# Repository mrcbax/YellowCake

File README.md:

# YellowCake

YellowCake is a UMW CPSC 491 project to create an open source, inexpensive, small footprint, single board, POSIX computer. YellowCake will be similar to a Raspberry Pi. The primary goal of the YellowCake project is learning. A secondary goal is to create a product that is used by others.

The members of the YellowCake team are the following.
- Gusty Cooper - faculty sponsor
- Chad Baxter - student researcher
- Collin Mistr - student researcher

Gusty is an experienced software developer and systems engineer. Chad and Collin are talented computer science students with lots of experience in electronic board design. They have designed several boards that fix problems in various MacBook computers. Their design solutions included board layout and subsequent manufacture by a foundry. Collin and Chad are selling their MacBook solutions on Ebay. A few of of their solutions are described at: 

- https://computeco.de/DyingLight
- https://computeco.de/MuxHat

## YellowCake Executive Summary

YellowCake is a research project to create an open source, single board computer similar to a Raspberry Pi. Chad and Collin will learn the fundamentals of building a computer, which include selecting a form factor of the board, selecting electronic components for a computer, designing communication among components, layout components on the board, printing the board, assembling a computer on the board, testing the computer, and establishing a LINUX operating system on the computer. The following is a picture of a Raspberry Pi single board computer.

## YellowCake Goals

YellowCake is a three credit CPSC 491, which occurs during Fall 2019. The goals for YellowCake are the following.
- Provide an environment in which Chad and Collin can significantly increase their CPSC skills and knowledge as related to computer architecture, design of single board computers, integration of electronics on single board computers, testing single board computers, and hosting and OS on single board computers.
- Complete the design YellowCake - the design is to be documented as open source.
- Complete the YellowCake board layout in a manufacturing format using the board CAD software KiCad: http://kicad-pcb.org/ - the layout is to be documented as open source.
- Complete a prototype of YellowCake - follow the process in YellowCake Design and Development Process to implement a prototype that demonstrates the design.

## YellowCake Prework

During Spring 2019, the YellowCake team will meet periodically to discuss the project, make preliminary decisions, define the parameters for CPSC 491 YellowCake, and submit funding requests. 
YellowCake Design Parameters
We have begun preliminary design, creating various design parameters. Design parameters are subject to change. The design parameters defined thus far are the following.
- YellowCake board.
  - Footprint will be small similar in size to Raspberry Pi.
  - YellowCake board footprint will adhere to a standard. The following are candidates.
     - PCI / 104 - Express:  https://pc104.org/hardware-specifications/pc104/
     - Intel NUC - https://www.intel.com/content/www/us/en/support/articles/000005545/mini-pcs.html
     - Pico-ITX - https://www.viatech.com/en/boards/pico-itx/ 
- YellowCake CPU Selection. We have had various ideas for YellowCake CPU. The primary option is to use an Intel family chip, which provide a large selection of LINUX operating systems. A design consideration is to select a CPU chip that is approximately $50. The following link shows several Intel options.
https://www.mouser.com/Semiconductors/Embedded-Processors-Controllers/CPU-Central-Processing-Units/_/N-ba96s?Keyword=intel+core&FS=True&Ns=Pricing|0

Some specific ideas we have considered are the following:
- Idea 1: Intel M series. The availability of Intel M chipsets may make the cost prohibitive.
- Idea 3: Intel Atom
- Idea 2: RISC-V. The availability of RISC-V chipsets may make the cost prohibitive.

YellowCake main memory. 
- Will be LPDDR3. DDR4 is newer and faster, but it costs significantly more than DDR3.

YellowCake secondary storage
- Will be eMMC technology.

YellowCake primary bus connecting CPU, Memory, and other devices 
- Will be determined.
YellowCake I/O
- USB-C NO: Atom does not support USB-C.YellowCake will include 1 USB-C port (if cpu choice supports it).
- USB-3:YellowCake will include 2 USB-3 ports.
- HDMI: YellowCake will include 1 HDMI port.
- WiFI: YellowCake will include wireless (a/b/g/n).
- Bluetooth: YellowCake will include bluetooth.

## YellowCake Design and Development Process

The YellowCake high-level design and development process (to be practiced in Fall 2019) consists of several cycles of design, produce, and test. The cycles continue until the final YellowCake product is created or funding diminishes. More details of design, produce, and test are the following.
- Design a rendition of the board.
- Submit the design to a foundry.
- Receive the board.
- Apply the components to the board.
- Test the board. 

## YellowCake Budget

We expect up to four iterations of the design process to achieve the final design. Total cost of the project is estimated to be $1000, which is $250 per design iteration. The detailed estimated cost of each design iteration is as follows.
- $75 - pay foundry to print the board.
- $50 - CPU SOC
- $25 - Memory components (BGA LPDDR3 4GB)
- $100 - support components (resistors, capacitors, connectors, ICs, ports,
headers, etc.)

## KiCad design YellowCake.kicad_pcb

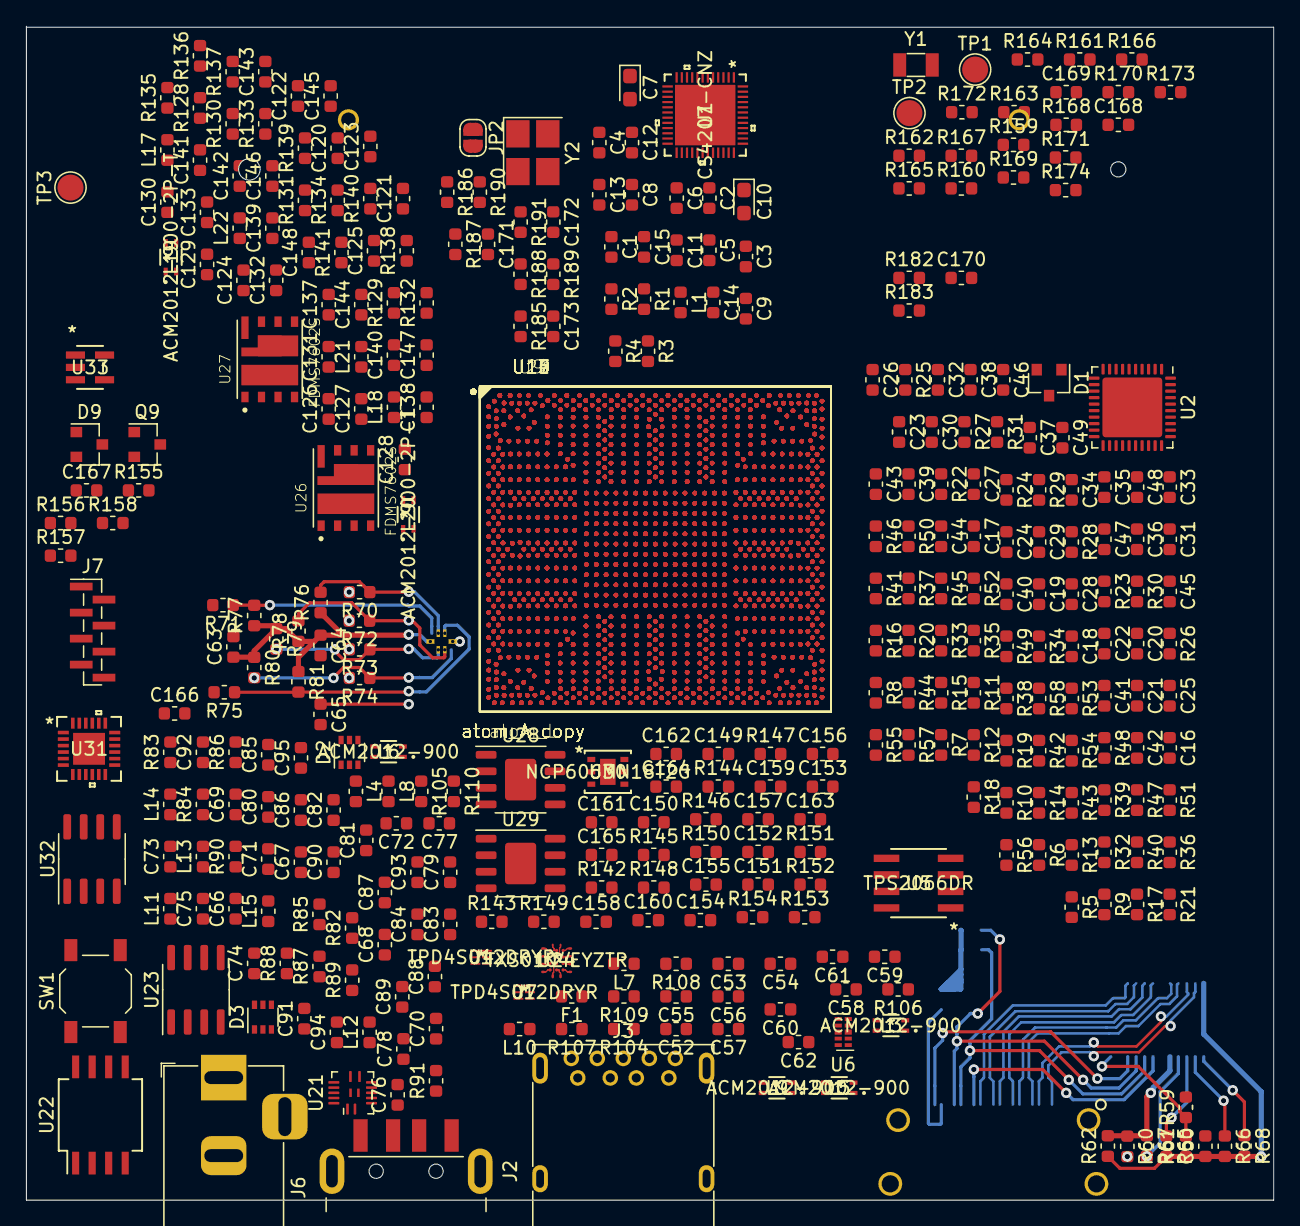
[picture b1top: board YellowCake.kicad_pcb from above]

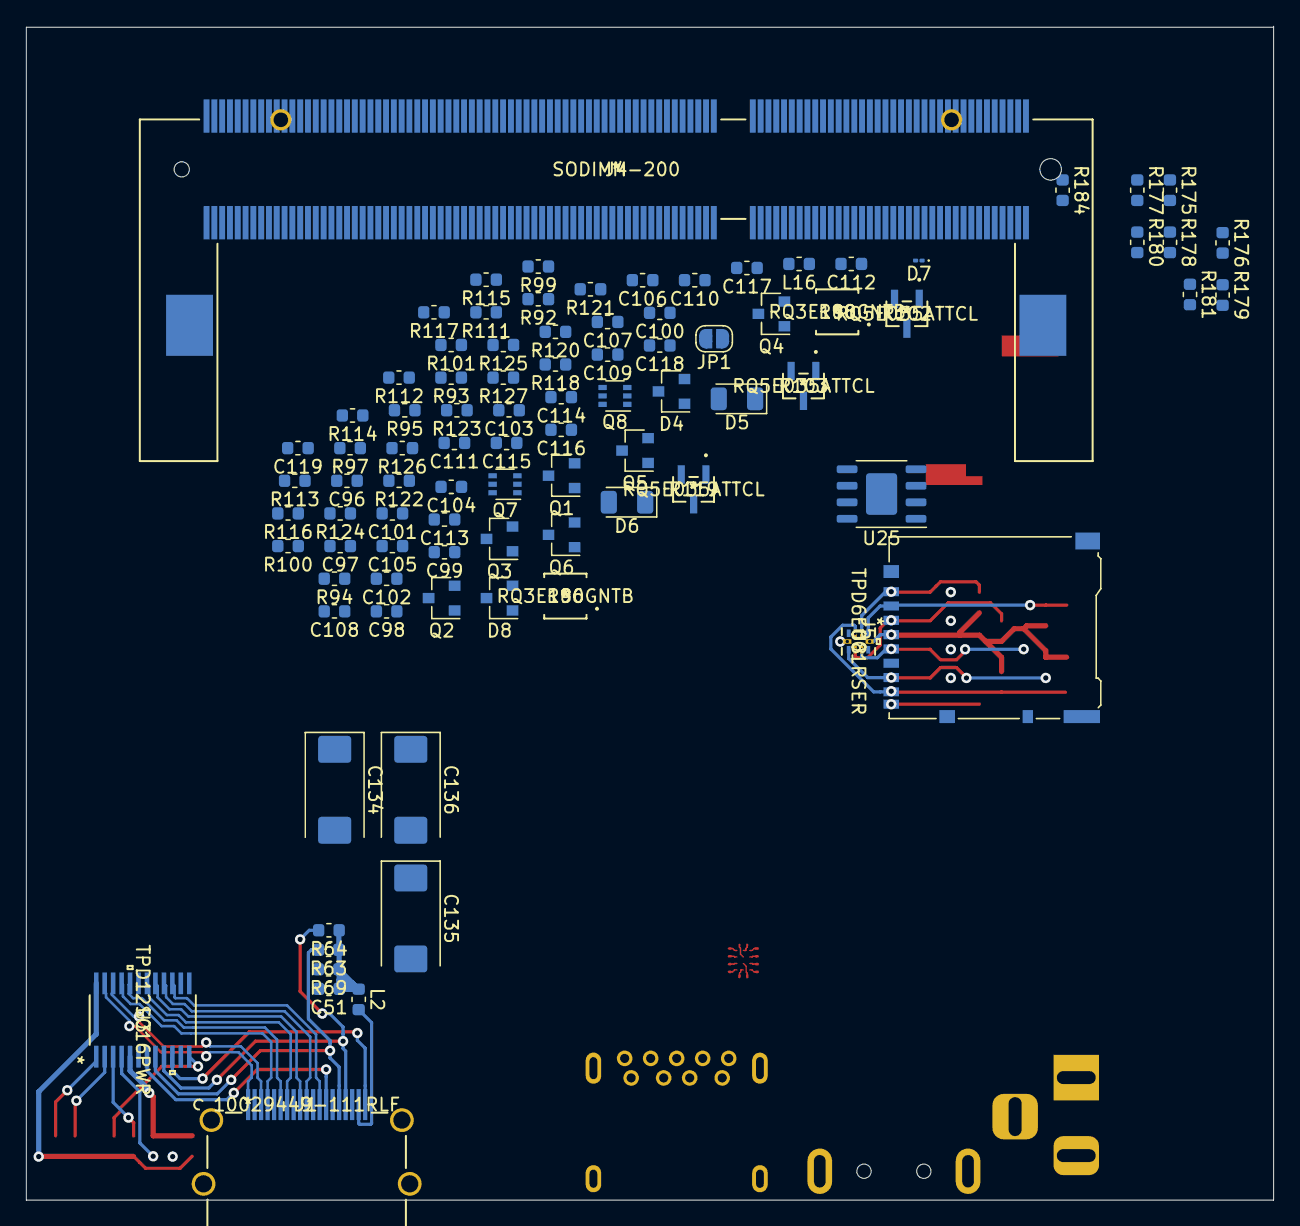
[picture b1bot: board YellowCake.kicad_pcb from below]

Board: 4 copper layers, 95.9 x 90.2 mm, 453 parts (90 on the bottom side), 264 nets.

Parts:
C1, C9, C11, C12, C14, C18, C21, C30, C34, C50, C52, C53, C54, C55, C56, C57, C58, C61, C62, C66, C69, C71, C78, C79, C80, C81, C82, C83, C84, C85, C86, C94, C95, C111, C113, C120, C121, C149, C151, C156, C157, C158, C159, C163, C166, C170: 0.1uF; C_0603_1608Metric
C2, C3, C6, C96, C98, C100, C119: 1uF; C_0603_1608Metric
C4, C5, C104, C105: 2.2uF; C_0603_1608Metric
C7, C10: 10uF; CP_EIA-2012-15_AVX-P
C8, C13, C15, C63, C64, C76, C89, C91, C97, C99, C102, C103, C110, C112, C114, C116, C118, C152, C160, C161, C162, C165: 10uF; C_0603_1608Metric
C16, C17, C31, C33: 1000pF; C_0603_1608Metric
C19, C22: 330pF; C_0603_1608Metric
C20, C23: 0.01uF; C_0603_1608Metric
C24, C28: 560pF; C_0603_1608Metric
C25: 470pF; C_0603_1608Metric
C26: 68pF; C_0603_1608Metric
C27: 220pF; C_0603_1608Metric
C29: 33pF; C_0603_1608Metric
C32, C35, C37, C72, C77, C117, C167: 1.0uF; C_0603_1608Metric
C36, C38, C39, C75: 0.22uF; C_0603_1608Metric
C40, C41, C126, C127: 2200pF; C_0603_1608Metric
C42, C43: 0.047uF; C_0603_1608Metric
C44, C45, C46, C47, C48, C49: 0.033uF; C_0603_1608Metric
C51: 4.7uF; C_0603_1608Metric
C59, C60, C67, C68, C70, C73, C74, C87, C88, C90, C92, C93, C122, C123, C124, C125, C128, C129, C130, C131, C132, C133, C137, C138, C139, C140, C141, C142, C143, C144, C145, C146, C147, C148, C150, C153: 22uF; C_0603_1608Metric
C65: 8200pF; R_0603_1608Metric
C101: 4700PF; C_0603_1608Metric
C106, C107, C108, C115, C164: 22pF; C_0603_1608Metric
C109, C171, C173: 27pF; C_0603_1608Metric
C134, C135, C136: 330uF; CP_EIA-7343-20_Kemet-V
C154, C155: 150pF; C_0603_1608Metric
C168, C169: 18pF; C_0603_1608Metric
C172: 10pF; C_0603_1608Metric
D1, D4, D8: BAT54A; SOT-23
D2, D3: BAV99S; SOT-363_SC-70-6
D5, D6: APTR3216-VFX; LED_1206_3216Metric
D7: D5V0L1B2LP-7B; D_01005_0402Metric
D9: BAT54C; SOT-23
F1: 2A; Fuse_0603_1608Metric
J1: 10029449-111RLF
J2: USB_A; USB_A_CNCTech_1001-011-01101_Horizontal
J3: USB3_A; USB3_A_Molex_48393-001
J4: SODIMM-200; 2013289-1
J5: Micro_SD_Card; microSD_HC_Hirose_DM3AT-SF-PEJM5
J6: Conn_Coaxial_Power; BarrelJack_Horizontal
J7: Conn_01x08_Male; PinHeader_1x08_P1.00mm_Vertical_SMD_Pin1Left
JP1, JP2: Jumper; SolderJumper-2_P1.3mm_Open_RoundedPad1.0x1.5mm
L1, L7, L8: 220Ohm; L_0603_1608Metric
L2: FB_220R_2.2A; L_0603_1608Metric
L3, L5, L6, L9: ACM2012-900; ACM2012-900-2P-T
L4, L10: 0Ohm; L_0603_1608Metric
L11, L12, L13, L14, L17, L18: FB_120R_3A; L_0603_1608Metric
L15: PIND-2.2U-8A; L_0603_1608Metric
L16: INDUCTOR; L_0603_1608Metric
L19, L20: ACM2012-900-2P-T
L21, L22: 0.33uH; L_0603_1608Metric
Q1, Q2, Q4, Q5, Q6: 2N7002K; SOT-23
Q3: MMBT3904; SOT-23
Q7, Q8: MBT3904DW1; SOT-363_SC-70-6
Q9: BSS138; SOT-23
R1, R2: 2.2kOhm; R_0603_1608Metric
R3, R4, R70, R71, R72, R73, R74, R75, R88: 33Ohm; R_0603_1608Metric
R5: 37.4KOhm; R_0603_1608Metric
R6, R144, R153, R154: 12.1KOhm; R_0603_1608Metric
R7, R8, R9, R10, R32, R34, R36, R38, R39, R42, R43, R59, R60, R67, R122, R128, R129, R130, R131, R140, R141, R150, R152, R166, R175, R176, R177, R178, R179, R180, R187, R188, R189, R190: 0Ohm; R_0603_1608Metric
R11, R12, R14, R15, R124: 10Ohm; R_0603_1608Metric
R13: 2.7KOhm; R_0603_1608Metric
R16: 2.32KOhm; R_0603_1608Metric
R17, R19: 200Ohm; R_0603_1608Metric
R18: 2.43KOhm; R_0603_1608Metric
R20, R23, R27: 80.6KOhm; R_0603_1608Metric
R21: 2.21KOhm; R_0603_1608Metric
R22, R24, R25: 69.8Ohm; R_0603_1608Metric
R26: 169KOhm; R_0603_1608Metric
R28, R30: 1.91KOhm; R_0603_1608Metric
R29, R31: 6.98KOhm; R_0603_1608Metric
R33: 16.9Ohm; R_0603_1608Metric
R35: 20Ohm; R_0603_1608Metric
R37, R90, R91, R94, R135, R138, R162: 1KOhm; R_0603_1608Metric
R40, R111, R136, R139: 1Ohm; R_0603_1608Metric
R41, R48: 18.7KOhm; R_0603_1608Metric
R44, R47: 3.83KOhm; R_0603_1608Metric
R45, R46: NTC-470KOhm; R_0603_1608Metric
R49, R50: 649Ohm; R_0603_1608Metric
R51: 2.67KOhm; R_0603_1608Metric
R52, R57: 2.61KOhm; R_0603_1608Metric
R53, R54: 11KOhm; R_0603_1608Metric
R55, R58: NTC-10KOhm; R_0603_1608Metric
R56: 2.55KOhm; R_0603_1608Metric
R61, R89, R104, R105, R109, R110, R182: 2.2KOhm; R_0603_1608Metric
R62: 2.2KOkm; R_0603_1608Metric
R63, R64, R65, R66, R68, R92, R93, R106, R107, R108, R132, R133, R146, R155, R156, R157, R158, R159, R161, R163, R164, R165, R181: 10KOhm; R_0603_1608Metric
R69, R76, R77, R78, R79, R80, R81, R85, R87, R95, R97, R100: 100KOhm; R_0603_1608Metric
R82, R84: 499KOhm; R_0603_1608Metric
R83: 2.2Ohms; R_0603_1608Metric
R86: 4.7Ohm; R_0603_1608Metric
R96, R98: RQ3E180GNTB
R99: 33KOhm; R_0603_1608Metric
R101: 200KOhm; R_0603_1608Metric
R102, R103, R119: RQ5E035ATTCL
R112: 148Ohm; R_0603_1608Metric
R113: 146Ohm; R_0603_1608Metric
R114, R115: 40.2KOhm; R_0603_1608Metric
R116: 1kOhm; R_0603_1608Metric
R117, R123: 10kOhm; R_0603_1608Metric
R118, R120, R121: 4.7kOhm; R_0603_1608Metric
R125: 200kOhm; R_0603_1608Metric
R126, R127: 20kOhm; R_0603_1608Metric
R134, R137: 2.2Ohm; R_0603_1608Metric
R142: 6.04KOhm; R_0603_1608Metric
R143: 23.7KOhm; R_0603_1608Metric
R145: 9.53KOhm; R_0603_1608Metric
R147, R148, R149, R151: 4.7KOhm; R_0603_1608Metric
R160: 402Ohm; R_0603_1608Metric
R167: 73.2Ohm; R_0603_1608Metric
R168, R169, R172: 49.9Ohm; R_0603_1608Metric
R170, R171, R184: 150Ohm; R_0603_1608Metric
R173: 357Ohm; R_0603_1608Metric
R174: 10MOhm; R_0603_1608Metric
R183: 420Ohm; R_0603_1608Metric
R185: 4.02KOhm; R_0603_1608Metric
R186: 47.5Ohm; R_0603_1608Metric
R191: 1MOhm; R_0603_1608Metric
SW1: SW_Push; SW_SPST_TL3342
TP1, TP2, TP3: TestPoint; TestPoint_Pad_D2.0mm
U1: CS4207-CNZ
U2: ISL95837HRZ-T; QFN-40-1EP_6x6mm_P0.5mm_EP4.6x4.6mm
U3: TPD12S016PWR
U4, U7: TPD4S012DRYR
U5: TPS2066DR
U6: TPD4EUSB30; USON-10_2.5x1.0mm_P0.5mm
U8: TPD6E001RSER
U9, U10, U11, U12, U13, U14, U15, U16, U17, U18, U19: atom_A_copy; FCBGA11702
U20: atom_L; FCBGA11702
U21: NB670; VQFN_EP
U22: IRF9321; SO-8_5.3x6.2mm_P1.27mm
U23: NCT3012S; SOIC-8_3.9x4.9mm_P1.27mm
U24: TXS0104EYZTR
U25: APL5912KAC; HTSOP-8-1EP_3.9x4.9mm_P1.27mm_EP2.4x3.2mm
U26, U27: FDMS7602S; TRANS_FDMD8530
U28, U29: APL5933; HTSOP-8-1EP_3.9x4.9mm_P1.27mm_EP2.4x3.2mm
U30: NCP606MN18T2G
U31: TS3A27518ERTWR
U32: 25LCxxx; SOIC-8_3.9x4.9mm_P1.27mm
U33: SN74LVC1G14DBVR
Y1: Crystal; Crystal_SMD_3215-2Pin_3.2x1.5mm
Y2: Crystal_GND24_Small; Crystal_SMD_3225-4Pin_3.2x2.5mm_HandSoldering

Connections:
1P5V_EN_B: Q7.5, Q7.6, R120.1
1P8V_EN: Q7.3, R121.1, R150.2
5VSB_CTRL: Q1.1, R90.1, R93.2, U23.8
+1V0: C21.1, R22.1, R24.1, R25.1
+3V3: C7.1, C9.1, C14.1, C63.1, C64.1, J5.4, R28.2, R30.2, R37.2, R76.1, R77.1, R78.1, R79.1, R80.1, R81.1, U1.1, U1.24, U1.25, U1.46, U8.10
+3VSB: C99.1, D9.1, J7.8, R103.3
+5VSB: C97.1, C101.1, C120.1, F1.1, L17.1, L18.1, Q6.3, R38.2, R40.2, R100.2, R101.1, R102.3, R103.2, R120.2, R148.2
+5VSB_SW: C121.1, C122.1, C123.1, C124.1, C125.1, C128.1, C129.1, C130.1, C131.1, C132.1, C133.1, L17.2, L18.2, R39.2, U26.2, U26.3, U26.4, U26.9, U27.2, U27.3, U27.4, U27.9
+10V: C85.2, D3.2, R95.1, R97.1, R99.1, R100.1
+HDMI_CRT_VCC: C51.1, L2.1, R63.1, R64.1, R69.1, U3.13
+PS_3VSB: C81.1, C87.1, C88.1, C90.1, C92.1, C93.1, C94.1, C156.1, C157.1, C160.1, C161.1, C162.2, L15.2, R91.2, R126.2, R149.1, U21.7, U28.3, U28.4, U29.3, U29.4, U30.1, U30.6
+PS_3VSB_PG: D4.1, R85.2, U21.4
+PS_5VSB: C78.2, C84.1, C86.1, C89.1, C91.1, C95.1, C104.1, D2.1, D5.2, L11.1, L12.1, R89.2, R90.2, R94.2, R118.1, U22.5, U22.6, U22.7, U22.8, U23.2
+USBVCC: C53.1, C54.1, C55.1, F1.2, R104.1, R105.1, U5.2, U24.B1
+V1P0A: C149.2, C150.1, C154.2, R142.2, U28.6
+V1P0A_PWRGD: D8.2, R152.2
+V1P8A: C164.1, C165.2, Q9.2, R92.2, R106.1, R153.1, U24.B2, U30.4
+V1P8S: C50.1, C151.2, C152.2, C153.1, C155.2, C170.1, R61.1, R62.1, R65.2, R66.2, R68.2, R125.1, R144.2, R151.1, R159.2, R161.2, R163.2, U3.24, U29.6, U33.5
+VCORE: C135.1, L19.3, L21.2, R14.1, R140.1
+VDIMM: C112.1, C114.1, R119.3, U25.5, U25.9
+VGFX: C134.1, C136.1, L20.3, L22.2, R11.1, R141.1
AUD_HP_GND: C1.2, C6.2, C8.2, C9.2, C10.2, C13.2, C14.2, C15.2, R3.2, R4.2, U1.26, U1.39
AUD_HP_OUT_L: C12.1, U1.38
AUD_HP_OUT_R: C11.2, U1.40
AUD_MIC_IN_L: C2.1, C3.2
DDP_1V8: C166.1, C167.1, J7.1, Q9.3, R155.2, R156.2, R157.2, R158.1, U31.5, U32.8
FP_PWRBTN: C113.1, D7.1, JP1.2, R88.2, R118.2, SW1.1
GFX_PG: C32.1, D1.2, R30.1, R32.2
GND: C16.2, C17.2, C18.2, C19.1, C20.2, C21.2, C22.1, C23.2, C30.2, C32.2, C34.2, C35.2, C36.2, C37.2, C48.2, C49.2, C50.2, C51.2, C53.2, C54.2, C55.2, C56.2, C59.2, C60.2, C62.2, C63.2, C64.2, C65.2, C66.2, C67.2, C68.2, C69.2, C70.2, C71.2, C72.2, C73.2, C74.2, C76.2, C77.2, C78.1, C80.1, C81.2, C84.2, C85.1, C86.2, C87.2, C88.2, C89.2, C90.2, C91.2, C92.2, C93.2, C94.2, C95.2, C96.2, C97.2, C98.2, C99.2, C100.2, C101.2, C102.2, C103.2, C104.2, C105.2, C106.2, C107.2, C108.2, C110.2, C111.2, C112.2, C113.2, C114.2, C115.2, C116.1, C117.1, C118.1, C119.1, C120.2, C121.2, C122.2, C123.2, C124.2, C125.2, C126.2, C127.2, C128.2, C129.2, C130.2, C131.2, C132.2, C133.2, C134.2, C135.2, C136.2, C137.2, C138.2, C139.2, C140.2, C141.2, C142.2, C143.2, C144.2, C145.2, C146.2, C147.2, C148.2, C149.1, C150.2, C151.1, C152.1, C153.2, C156.2, C157.2, C158.2, C159.2, C160.2, C161.2, C162.1, C163.2, C165.1, C166.2, C167.2, C168.1, C169.1, C170.2, C171.2, C172.1, C173.1, D7.2, J1.2, J1.5, J1.8, J1.11, J1.17, J2.4, J2.5, J3.4, J3.7, J3.10, J5.6, J6.2, J7.2, JP1.1, L4.1, L10.1, Q1.2, Q2.2, Q3.2, Q4.2, Q5.2, Q6.2, Q7.1, Q7.4, Q8.1, Q8.4, R6.2, R8.2, R12.2, R15.2, R26.2, R27.2, R41.1, R45.1, R46.1, R48.1, R69.2, R82.2, R87.1, R101.2, R107.2, R108.2, R109.2, R110.2, R111.2, R112.1, R113.1, R114.2, R143.2, R145.2, R146.1, R147.1, R154.2, R160.1, R164.2, R165.2, R168.2, R169.1, R170.1, R171.1, R172.1, R173.1, R175.2, R176.2, R177.2, R178.2, R179.2, R180.2, R181.1, R182.1, R184.2, R185.1, R186.2, SW1.2, U2.27, U3.6, U3.14, U3.19, U4.4, U5.1, U6.3, U6.8, U7.4, U8.5, U9.AY3, U10.A3, U10.A5, U10.A6, U10.A11, U10.A15, U10.A19, U10.A23, U10.A27, U10.A31, U10.A35, U10.A39, U10.A43, U10.A47, U10.A49, U10.A51, U10.A52, U10.AA1, U10.AA3, U10.AA16, U10.AA19, U10.AA21, U10.AA32, U10.AA35, U10.AA38, U10.AA53, U10.AB4, U10.AB6, U10.AB10, U10.AB41, U10.AB45, U10.AB47, U10.AB48, U10.AB50, U10.AB51, U10.AC16, U10.AC18, U10.AC19, U10.AC21, U10.AC25, U10.AC33, U10.AC35, U10.AC36, U10.AC38, U10.AD7, U10.AD19, U10.AD21, U10.AD25, U10.AD32, U10.AD33, U10.AD47, U10.AE1, U10.AE3, U10.AE4, U10.AE6, U10.AE8, U10.AE9, U10.AE11, U10.AE12, U10.AE14, U10.AE40, U10.AE42, U10.AE43, U10.AE45, U10.AE46, U10.B2, U10.B52, U10.B53, U10.C1, U10.C14, U10.C31, U10.C34, U10.C39, U10.C42, U10.C45, U10.C49, U10.C53, U10.D12, U10.D16, U10.D24, U10.D30, U10.D36, U10.D38, U10.E1, U10.E8, U10.E19, U10.E35, U10.E53, U10.F2, U10.F5, U10.F7, U10.F19, U10.F24, U10.F27, U10.F30, U10.F35, U10.G10, U10.G20, U10.G22, U10.G26, U10.G28, U10.G32, U10.G34, U10.G42, U10.J35, U10.J40, U10.J53, U10.K4, U10.K9, U10.K14, U10.K22, U10.K32, U10.K36, U10.K50, U10.L13, U10.L19, U10.L27, U10.L35, U10.M19, U10.M26, U10.M27, U10.M28, U10.M34, U10.M35, U10.M38, U10.M47, U10.M51, U10.N1, U10.N16, U10.N38, U10.N51, U10.P4, U10.P9, U10.P13, U10.P16, U10.P19, U10.P20, U10.P24, U10.P32, U10.P35, U10.P38, U10.P47, U10.P52, U10.T40, U10.U1, U10.U3, U10.U5, U10.U6, U10.U8, U10.U9, U10.U11, U10.U12, U10.U14, U10.U21, U10.U30, U10.U32, U10.U40, U10.U42, U10.U43, U10.U45, U10.U46, U10.U48, U10.U49, U10.U51, U10.U53, U10.V7, U10.V12, U10.V16, U10.V19, U10.V21, U10.V35, U10.V40, U10.V44, U10.V51, U10.Y7, U10.Y9, U10.Y10, U10.Y14, U10.Y16, U10.Y21, U10.Y25, U10.Y33, U10.Y41, U10.Y44, U11.AE48, U11.AE50, U11.AE51, U11.AE53, U11.AF10, U11.AF12, U11.AF25, U11.AF32, U11.AF47, U11.AG16, U11.AG25, U11.AG36, U11.AG38, U11.AH4, U11.AH6, U11.AH7, U11.AH9, U11.AH41, U11.AH45, U11.AH47, U11.AH48, U11.AH50, U11.AH51, U11.AJ1, U11.AJ3, U11.AJ16, U11.AJ21, U11.AJ25, U11.AJ27, U11.AJ29, U11.AJ30, U11.AJ32, U11.AJ33, U11.AJ35, U11.AJ38, U11.AJ53, U11.AK10, U11.AK14, U11.AK16, U11.AK33, U11.AK41, U11.AK44, U11.AM7, U11.AM12, U11.AM19, U11.AM24, U11.AM25, U11.AM29, U11.AM33, U11.AM35, U11.AM36, U11.AM40, U11.AM44, U11.AM51, U11.AN1, U11.AN3, U11.AN5, U11.AN6, U11.AN8, U11.AN9, U11.AN11, U11.AN12, U11.AN14, U11.AN16, U11.AN22, U11.AN33, U11.AN35, U11.AN36, U11.AN38, U11.AN40, U11.AN42, U11.AN43, U11.AN45, U11.AN46, U11.AN48, U11.AN49, U11.AN51, U11.AN53, U11.AP40, U11.AT4, U11.AT12, U11.AT16, U11.AT19, U11.AT24, U11.AT27, U11.AT30, U11.AT35, U11.AT38, U11.AT47, U11.AT52, U11.AU1, U11.AU3, U11.AU24, U11.AU30, U11.AU38, U11.AU51, U11.AV7, U11.AV12, U11.AV13, U11.AV14, U11.AV18, U11.AV19, U11.AV24, U11.AV27, U11.AV30, U11.AV35, U11.AV38, U11.AV47, U11.AV51, U11.AW3, U11.AW13, U11.AW19, U11.AW27, U11.AW35, U11.AY4, U11.AY9, U11.AY10, U11.AY22, U11.AY32, U11.AY36, U11.AY50, U11.BA14, U11.BA19, U11.BA22, U11.BA27, U11.BA32, U11.BA35, U11.BA40, U11.BA53, U11.BB19, U11.BB27, U11.BB35, U11.BC20, U11.BC22, U11.BC26, U11.BC28, U11.BC32, U11.BC34, U11.BC42, U11.BD19, U11.BD24, U11.BD27, U11.BD30, U11.BD35, U11.BE1, U11.BE2, U11.BE8, U11.BE19, U11.BE35, U11.BE53, U11.BF4, U11.BF12, U11.BF16, U11.BF24, U11.BF30, U11.BF36, U11.BF38, U11.BG1, U11.BG31, U11.BG34, U11.BG39, U11.BG42, U11.BG45, U11.BG49, U11.BG53, U11.BH1, U11.BH2, U11.BH52, U11.BH53, U11.BJ2, U11.BJ3, U11.BJ5, U11.BJ7, U11.BJ11, U11.BJ15, U11.BJ19, U11.BJ23, U11.BJ27, U11.BJ31, U11.BJ35, U11.BJ39, U11.BJ43, U11.BJ47, U11.BJ49, U11.BJ51, U11.BJ52, U18.G30, U18.K30, U21.2, U21.14, U24.D2, U25.1, U26.5, U26.6, U26.7, U27.5, U27.6, U27.7, U28.8, U28.9, U29.8, U29.9, U30.2, U30.7, U31.2, U31.7, U31.9, U31.17, U32.4, U33.3
GPIO_s0_SC_56: R163.1, R164.1
HDMI_CEC: R68.1, U3.1
HDMI_CLK_DN: J1.12, U3.15, U18.AP2
HDMI_CLK_DP: J1.10, U3.16, U18.AP3
HDMI_DDCCLK: R66.1, U3.2, U18.C27
HDMI_DDCDAT: R65.1, U3.3, U18.C26
HDMI_TX0_DN: J1.9, U3.17, U18.AR1
HDMI_TX0_DP: J1.7, U3.18, U18.AR3
HDMI_TX1_DN: J1.6, U3.20, U18.AT3
HDMI_TX1_DP: J1.4, U3.21, U18.AT2
HDMI_TX2_DN: J1.3, U3.22, U18.AV2
HDMI_TX2_DP: J1.1, U3.23, U18.AV3
ISUMPG_R: R55.2, R56.1
ISUMP_R: R57.1, R58.2
LGATE1: R128.1, U2.24
LGATEG: R130.1, U2.31
unnamed: C1.1, L1.2, U1.3, U1.9
unnamed: C2.2, R1.1, U1.18
unnamed: C3.1, R2.1, U1.19
unnamed: C4.1, U1.45
unnamed: C4.2, C5.1, U1.43
unnamed: C5.2, U1.42
unnamed: C6.1, U1.27
unnamed: C7.2, U1.29
unnamed: C8.1, U1.28
unnamed: C11.1, R3.1
unnamed: C12.2, R4.1
unnamed: C13.1, U1.44
unnamed: C15.1, U1.41
unnamed: C16.1, R13.2
unnamed: C17.1, R16.2
unnamed: C18.1, R5.2, R6.1, U2.6
unnamed: C19.2, C24.1, R7.1, R11.2, R18.1
unnamed: C20.1, R8.1, R12.1, U2.38
unnamed: C22.2, C27.1, R9.1, R14.2, R21.1
unnamed: C23.1, R10.1, R15.1, U2.16
unnamed: C24.2, R17.1
unnamed: C25.1, C26.1, C31.2, R26.1, R29.1, U2.40
unnamed: C25.2, R20.1
unnamed: C26.2, R13.1, R17.2, R18.2, R20.2, U2.39
unnamed: C27.2, R19.1
unnamed: C28.1, C29.1, C33.2, R27.1, R31.1, U2.11
unnamed: C28.2, R23.1
unnamed: C29.2, R16.1, R19.2, R21.2, R23.2, U2.12
unnamed: C31.1, R29.2, U2.1
unnamed: C33.1, R31.2, U2.10
unnamed: C35.1, R38.1, U2.26
unnamed: C36.1, R39.1, U2.20
unnamed: C37.1, R40.1, U2.19
unnamed: C38.2, R42.1
unnamed: C39.2, R43.1
unnamed: C40.2, R49.1
unnamed: C41.2, R50.1
unnamed: C52.2, L4.2
unnamed: C57.2, L5.1
unnamed: C58.2, L5.3
unnamed: C61.2, L10.2
unnamed: C65.1, J5.9
unnamed: C66.1, C69.1, J6.1, L13.2, L14.2, R83.1
unnamed: C67.1, C68.1, C70.1, C73.1, C74.1, L11.2, L12.2, R84.1, U21.1
unnamed: C71.1, R82.1, R84.2, U21.13
unnamed: C72.1, R83.2
unnamed: C75.1, L13.1, L14.1, U22.1, U22.2, U22.3
unnamed: C75.2, R87.2, U22.4
unnamed: C76.1, U21.6
unnamed: C77.1, R85.1, U21.11
unnamed: C79.1, D2.6
unnamed: C79.2, C83.2, U21.5
unnamed: C80.2, D2.2, D3.1
unnamed: C82.1, R86.1
unnamed: C82.2, L15.1, U21.8, U21.9, U21.15, U21.16
unnamed: C83.1, D3.6
unnamed: C96.1, Q2.1, R93.1
unnamed: C98.1, Q2.3, R95.2
unnamed: C100.1, Q4.3, R97.2
unnamed: C109.2, R115.2, U25.2
unnamed: C111.1, R116.1, R119.2
unnamed: C117.2, R124.2, U25.6
unnamed: C119.2, D8.3, Q8.2, R125.2
unnamed: C126.1, R134.2
unnamed: C127.1, R137.2
unnamed: C137.1, C139.1, C141.1, C143.1, C145.1, R140.2
unnamed: C138.1, C140.1, C142.1, C144.1, C146.1, C147.1, C148.1, R141.2
unnamed: C154.1, R142.1, R143.1, U28.7
unnamed: C155.1, R144.1, R145.1, U29.7
unnamed: C158.1, R146.2, R148.1, U28.2
unnamed: C159.1, R147.2, R150.1, U29.2
unnamed: C163.1, R152.1, U30.3
unnamed: C164.2, R153.2, R154.1, U30.5
unnamed: C168.2, R174.1, U9.A9, Y1.1
unnamed: C169.2, R174.2, U9.C9, Y1.2
unnamed: C171.1, R191.1, U9.AH12, Y2.1
unnamed: C173.2, R191.2, U9.AH10, Y2.3
unnamed: D4.2, Q3.3, Q4.1, R94.1
unnamed: D5.1, R112.2
unnamed: D6.1, R113.2
unnamed: D9.3, Q9.1, U31.11, U31.21
unnamed: J1.13, U3.7
unnamed: J1.15, R63.2, U3.8
unnamed: J1.16, R64.2, U3.9
unnamed: J1.18, L2.2
unnamed: J1.19, U3.10
unnamed: J2.2, L3.2, U4.1
unnamed: J2.3, L3.4, U4.2
unnamed: J3.2, L9.4, U7.2
unnamed: J3.3, L9.2, U7.1
unnamed: J3.5, L6.4, U6.5
unnamed: J3.6, L6.2, U6.4
unnamed: J3.8, L5.4, U6.2
unnamed: J3.9, L5.2, U6.1
unnamed: J5.1, R70.1, R76.2, U8.2
unnamed: J5.2, R71.1, R77.2, U8.1
unnamed: J5.3, R72.1, R78.2, U8.7
unnamed: J5.5, R73.1, R79.2, U8.8
unnamed: J5.7, R74.1, R80.2, U8.6
unnamed: J5.8, R75.1, R81.2, U8.3
unnamed: J7.3, R158.2, U31.18
unnamed: J7.4, U31.23
unnamed: J7.5, U31.20
unnamed: J7.6, U31.22
unnamed: JP2.1, R159.1
unnamed: JP2.2, R160.2, U9.BD5
unnamed: L7.1, U5.7
unnamed: L8.1, U5.6
unnamed: L19.1, R135.2
unnamed: L19.2, R136.2
unnamed: L20.1, R138.2
unnamed: L20.2, R139.2
unnamed: Q1.3, Q3.1, R92.1
unnamed: Q5.3, Q6.1, R99.2
unnamed: Q7.2, R117.2
unnamed: Q8.5, Q8.6, R126.1
unnamed: R1.2, R2.2, U1.16
unnamed: R32.1, U2.2
unnamed: R33.1, U2.3
unnamed: R34.1, U2.4
unnamed: R35.1, U2.5
unnamed: R36.1, U2.7
unnamed: R41.2, R44.1, R45.2
unnamed: R42.2, U2.34
unnamed: R43.2, U2.21
unnamed: R44.2, U2.9
unnamed: R46.2, R47.1, R48.2
unnamed: R47.2, U2.35
unnamed: R49.2, R51.2, U2.36
unnamed: R50.2, R52.2, U2.17
unnamed: R59.1, R61.2, U3.12
unnamed: R60.1, R62.2, R67.1, U3.5
unnamed: R67.2, U3.4
unnamed: R86.2, U21.10
unnamed: R88.1, U23.3
unnamed: R89.1, U23.1
unnamed: R106.2, U24.B3
unnamed: R122.1, U25.8
unnamed: R123.1, U25.7
unnamed: R128.2, U26.8
unnamed: R129.2, R132.2, U26.1
unnamed: R130.2, U27.8
unnamed: R131.2, R133.2, U27.1
unnamed: R149.2, U28.1
unnamed: R151.2, U29.1
unnamed: R155.1, U31.6, U32.1
unnamed: R162.2, R165.1
unnamed: R168.1, U9.BF26
unnamed: R169.2, U9.BF20
unnamed: R170.2, U9.BC2
unnamed: R171.2, U9.BC1
unnamed: R172.2, U9.AY18
unnamed: R173.2, U9.AW1
unnamed: R175.1, U17.AH2
unnamed: R176.1, U17.AH3
unnamed: R177.1, U17.AM2
unnamed: R178.1, U17.AM3
unnamed: R179.1, U17.BB5
unnamed: R180.1, U17.BB7
unnamed: R181.2, U17.A29
unnamed: R182.2, U18.P30
unnamed: R183.1, U18.AK12
unnamed: R183.2, U18.AK13
unnamed: R184.1, U20.P14
unnamed: R185.2, U9.AD14
unnamed: R186.1, U9.AD13
unnamed: R187.1, U9.A21
unnamed: R188.2, U9.B22
unnamed: R189.1, U9.C23
unnamed: R190.1, U9.C22
unnamed: TP1.1, U9.BD22
unnamed: TP2.1, U9.BF22
unnamed: TP3.1, U17.B30
unnamed: U18.D27, U33.4
unnamed: U31.1, U32.6
unnamed: U31.3, U32.5
unnamed: U31.4, U32.2
PHASE1: C39.1, L19.4, L21.1, R132.1, R134.1, U2.23, U26.10
PHASEG: C38.1, L20.4, L22.1, R133.1, R137.1, U2.32, U27.10
PS_OUT_L: R91.1, U23.7
SD3_CD#: R166.1, U9.BC24
SD3_CLK: R73.2, U9.AY26
SD3_CMD: R72.2, U9.AV28
SD3_D0: R74.2, U9.AT28
SD3_D1: R75.2, U9.BD26
SD3_D2: R70.2, U9.AU28
SD3_D3: R71.2, U9.BA26
SLP_S3_L: D8.1, Q5.1
SOC_SPI_CLK-R: C172.2, R190.2, U31.8
SOC_SPI_MISO-R: R188.1, U31.12
SOC_SPI_MOSI-R: R187.2, U31.10
SOC_USB_HOST_EN0: R109.1, U24.C2
SOC_USB_HOST_EN1: R110.1, U24.D3
SPI_HOLD: R156.1, U32.7
SPI_WP: R157.1, U32.3
SVID_ALERT-R: R24.2, R34.2
SVID_CLK-R: R25.2, R35.2
SVID_DATA-R: R22.2, R33.2
SYS_PWRGD: Q8.3, R127.2
UGATE1: R129.1, U2.22
UGATEG: R131.1, U2.33
USB_HOST_EN0: R108.1, U5.3, U24.A2
USB_HOST_EN1: R107.1, U5.4, U24.D1
USB_HOST_OC0: R105.2, U5.8, U24.A1
USB_HOST_OC1: R104.2, U5.5, U24.A3
V1P05S: C106.1, C107.1, C108.1, C109.1, C110.1, R114.1, R115.1, R167.2, U25.3, U25.4
V1P35S: C115.1, C116.2, R117.1, R119.1
VBUS1: C60.1, C61.1, C62.1, J3.1, L7.2, U7.6
VBUS2: C52.1, C56.1, C59.1, J2.1, L8.2, U4.6
VCC: C102.1, C105.1, D6.2, R5.1, R102.1, R121.2, R123.2, R124.1
VCC3: C103.1, L16.1, R103.1, R127.1
VCC3S: C118.2, L16.2
VCORE_GFX_PG: C34.1, D1.3, R37.1, R122.2
VCORE_PG: C30.1, D1.1, R28.1, R36.2
VR_HOT_L: R167.1, U2.8, U9.C24
VSUMN: C41.1, C43.1, C45.1, C47.1, C49.1, R52.1, R54.1, R58.1, R136.1
VSUMNG: C40.1, C42.1, C44.1, C46.1, C48.1, R51.1, R53.1, R55.1, R139.1
VSUMP: C43.2, C45.2, C47.2, R54.2, R57.2, R135.1, U2.18
VSUMPG: C42.2, C44.2, C46.2, R53.2, R56.2, R138.1, U2.37

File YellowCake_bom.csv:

Reference,Quantity,Value,Footprint,Datasheet,Type,Rating,Price Per Unit,Net,Notes
C1 C14 C11 C12 C9 C18 C30 C21 C34 C55 C58 C73 C75 C60 C67 C69 C74 C68 C72 C71 C70 C83,22,0.1uF,Capacitor_SMD:C_0603_1608Metric,~,,,$0.01,$0.22,
C22 C19,2,330pF,Capacitor_SMD:C_0603_1608Metric,~,,,$0.01,$0.02,
C23 C20,2,0.01uF,Capacitor_SMD:C_0603_1608Metric,~,,,$0.01,$0.02,
C25,1,470pF,Capacitor_SMD:C_0603_1608Metric,~,,,$0.01,$0.01,
C26,1,68pF,Capacitor_SMD:C_0603_1608Metric,~,,,$0.01,$0.01,
C27,1,220pF,Capacitor_SMD:C_0603_1608Metric,~,,,$0.01,$0.01,
C28 C24,2,560pF,Capacitor_SMD:C_0603_1608Metric,~,,,$0.01,$0.02,
C29,1,33pF,Capacitor_SMD:C_0603_1608Metric,~,,,$0.01,$0.01,
C32 C35 C37 C61 C66,5,1.0uF,Capacitor_SMD:C_0603_1608Metric,~,,,$0.01,$0.05,
C33 C17 C31 C16,4,1000pF,Capacitor_SMD:C_0603_1608Metric,~,,,$0.01,$0.04,
C39 C38 C36 C64,4,0.22uF,Capacitor_SMD:C_0603_1608Metric,~,,,$0.01,$0.04,
C4 C5,2,2.2uF,Capacitor_SMD:C_0603_1608Metric,~,CERM_LESR,,$0.05,$0.10,
C41 C40,2,2200pF,Capacitor_SMD:C_0603_1608Metric,~,,,$0.01,$0.02,
C43 C42,2,0.047uF,Capacitor_SMD:C_0603_1608Metric,~,,,$0.01,$0.02,
C47 C45 C46 C44 C49 C48,6,0.033uF,Capacitor_SMD:C_0603_1608Metric,~,,,$0.01,$0.06,
C50,1,0.1uF,,~,,,$0.01,$0.01,
C51,1,4.7uF,,~,,,$0.01,$0.01,
C52 C53,2,10uF,,~,,,$0.01,$0.02,
C54,1,8200pF,Resistor_SMD:R_0603_1608Metric,~,,1000v,$0.01,$0.01,
C56 C57 C59 C62 C63 C76 C77 C79 C81 C82,10,22uF,Capacitor_SMD:C_0603_1608Metric,~,,,$0.01,$0.10,
C6 C2 C3,3,1uF,Capacitor_SMD:C_0603_1608Metric,~,,,$0.01,$0.03,
C7 C10,2,10uF,Capacitor_Tantalum_SMD:CP_EIA-2012-15_AVX-P,~,TANT,,$0.05,$0.10,
C8 C13 C15 C78 C80 C65,6,10uF,Capacitor_SMD:C_0603_1608Metric,~,,,$0.01,$0.06,
D1,1,BAT54A,Package_TO_SOT_SMD:SOT-23,http://www.diodes.com/_files/datasheets/ds11005.pdf,,,$0.10,$0.10,
D2 D3,2,BAV99S,Package_TO_SOT_SMD:SOT-363_SC-70-6,https://assets.nexperia.com/documents/data-sheet/BAV99_SER.pdf,,,$0.40,$0.80,
J1,1,HDMI_A,,https://en.wikipedia.org/wiki/HDMI,,,$0.00,$0.00,Purchased
J2,1,SODIMM-200,,,,,$0.00,$0.00,Purchased
J3,1,Micro_SD_Card,,http://katalog.we-online.de/em/datasheet/693072010801.pdf,,,$0.00,$0.00,Purchased
J4,1,Conn_Coaxial_Power,,~,,,$0.00,$0.00,Purchased
L1,1,220Ohm,Inductor_SMD:L_0603_1608Metric,~,,,$0.05,$0.05,
L2,1,FB_220R_2.2A,Inductor_SMD:L_0603_1608Metric,~,,,$0.05,$0.05,
L5 L6 L3 L4,4,FB_120R_3A,Inductor_SMD:L_0603_1608Metric,~,,,$0.05,$0.20,
L7,1,PIND-2.2U-8A,Inductor_SMD:L_0603_1608Metric,~,,,$0.05,$0.05,
R1 R2,2,2.2kOhm,Resistor_SMD:R_0603_1608Metric,~,,,$0.01,$0.02,
R13,1,2.7KOhm,Resistor_SMD:R_0603_1608Metric,~,,,$0.01,$0.01,
R14 R15 R11 R12,4,10Ohm,Resistor_SMD:R_0603_1608Metric,~,,,$0.01,$0.04,
R16,1,2.32KOhm,Resistor_SMD:R_0603_1608Metric,~,,,$0.01,$0.01,
R18,1,2.43KOhm,Resistor_SMD:R_0603_1608Metric,~,,,$0.01,$0.01,
R19 R17,2,200Ohm,Resistor_SMD:R_0603_1608Metric,~,,,$0.01,$0.02,
R21,1,2.21KOhm,Resistor_SMD:R_0603_1608Metric,~,,,$0.01,$0.01,
R23 R20 R27,3,80.6KOhm,Resistor_SMD:R_0603_1608Metric,~,,,$0.01,$0.03,
R25 R24 R22,3,69.8Ohm,Resistor_SMD:R_0603_1608Metric,~,,,$0.01,$0.03,
R26,1,169KOhm,Resistor_SMD:R_0603_1608Metric,~,,,$0.01,$0.01,
R30 R28,2,1.91KOhm,Resistor_SMD:R_0603_1608Metric,~,,,$0.01,$0.02,
R31 R29,2,6.98KOhm,Resistor_SMD:R_0603_1608Metric,~,,,$0.01,$0.02,
R33,1,16.9Ohm,Resistor_SMD:R_0603_1608Metric,~,,,$0.01,$0.01,
R34 R32 R36 R9 R10 R7 R8 R43 R42 R38 R39,11,0Ohm,Resistor_SMD:R_0603_1608Metric,~,,,$0.01,$0.11,
R35,1,20Ohm,Resistor_SMD:R_0603_1608Metric,~,,,$0.01,$0.01,
R37,1,1KOhm,Resistor_SMD:R_0603_1608Metric,~,,,$0.01,$0.01,
R4 R3 R75 R74 R73 R72 R71 R70,8,33Ohm,Resistor_SMD:R_0603_1608Metric,~,,,$0.01,$0.08,
R40,1,1Ohm,Resistor_SMD:R_0603_1608Metric,~,,,$0.01,$0.01,
R41 R48,2,18.7KOhm,Resistor_SMD:R_0603_1608Metric,~,,,$0.01,$0.02,
R44 R47,2,3.83KOhm,Resistor_SMD:R_0603_1608Metric,~,,,$0.01,$0.02,
R45 R46,2,NTC-470KOhm,Resistor_SMD:R_0603_1608Metric,~,,,$0.01,$0.02,
R5,1,37.4KOhm,Resistor_SMD:R_0603_1608Metric,~,,,$0.01,$0.01,
R50 R49,2,649Ohm,Resistor_SMD:R_0603_1608Metric,~,,,$0.01,$0.02,
R51,1,2.67KOhm,Resistor_SMD:R_0603_1608Metric,~,,,$0.01,$0.01,
R54 R53,2,11KOhm,Resistor_SMD:R_0603_1608Metric,~,,,$0.01,$0.02,
R56,1,2.55KOhm,Resistor_SMD:R_0603_1608Metric,~,,,$0.01,$0.01,
R57 R52,2,2.61KOhm,Resistor_SMD:R_0603_1608Metric,~,,,$0.01,$0.02,
R58 R55,2,NTC-10KOhm,Resistor_SMD:R_0603_1608Metric,~,,,$0.01,$0.02,
R59 R60 R67,3,0Ohm,Resistor_SMD:R_0603_1608Metric,~,,,$0.01,$0.03,
R6,1,12.1KOhm,Resistor_SMD:R_0603_1608Metric,~,,,$0.01,$0.01,
R61,1,2.2KOhm,Resistor_SMD:R_0603_1608Metric,~,,,$0.01,$0.01,
R62,1,2.2KOkm,Resistor_SMD:R_0603_1608Metric,~,,,$0.01,$0.01,
R63 R64 R65 R66 R68,5,10KOhm,Resistor_SMD:R_0603_1608Metric,~,,,$0.01,$0.05,
R69,1,100KOhm,Resistor_SMD:R_0603_1608Metric,~,,,$0.01,$0.01,
R76 R77 R78 R79 R80 R81 R87 R85,8,100KOhm,Resistor_SMD:R_0603_1608Metric,~,,,$0.01,$0.08,
R83,1,2.2Ohms,Resistor_SMD:R_0603_1608Metric,~,,,$0.01,$0.01,
R84 R82,2,499KOhm,Resistor_SMD:R_0603_1608Metric,~,,,$0.01,$0.02,
R86,1,4.7Ohm,Resistor_SMD:R_0603_1608Metric,~,,,$0.01,$0.01,
U1,1,CS4207-CNZ,CIR-QFN-48_6X6,,,,$10.00,$10.00,
U10,1,atom_F,,,,,$0.00,$0.00,Purchased
U11,1,atom_G,,,,,$0.00,$0.00,Purchased
U12,1,atom_H,,,,,$0.00,$0.00,Purchased
U13,1,atom_I,,,,,$0.00,$0.00,Purchased
U14,1,atom_J,,,,,$0.00,$0.00,Purchased
U15,1,atom_K,,,,,$0.00,$0.00,Purchased
U16,1,atom_L,,,,,$0.00,$0.00,Purchased
U17,1,NB670,,,,,$3.00,$3.00,
U18,1,IRF9321,,,,,$4.00,$4.00,
U2,1,ISL95837HRZ-T,Package_DFN_QFN:QFN-40-1EP_6x6mm_P0.5mm_EP4.6x4.6mm,,,,$4.00,$4.00,
U3,1,TPD12S016PWR,PW24,,,,$2.00,$2.00,
U4,1,TPD6E001RSER,TPD6E001RSER:TPD6E001RSER,,,,$0.60,$0.60,
U5,1,atom_A,,,,,$0.00,$0.00,Purchased
U6,1,atom_B,,,,,$0.00,$0.00,Purchased
U7,1,atom_C,,,,,$0.00,$0.00,Purchased
U8,1,atom_D,,,,,$0.00,$0.00,Purchased
U9,1,atom_E,,,,,$0.00,$0.00,Purchased
_,_,_,_,_,Overrun Buffer,$20.00,Total,$46.71,

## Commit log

2019-05-24 added kicad project
2019-05-24 added datasheets
2019-05-24 made image smaller
2019-09-03 added parts list and schedule, swapped cpu
2019-09-03 added pci/104 headers to parts list
2019-09-05 added links
2019-09-05 updated schedule
2019-09-05 added time for visit
2019-09-12 added totals
2019-09-17 added cost breakdown
2019-10-01 started power supply and DAC circuitry
2019-10-02 splitting cpu
2019-10-02 added schematic plot
2019-10-08 powersupply
2019-10-09 rest of power controller
2019-10-16 worked on HDMI and paper
2019-10-23 finished SDCARD
2019-10-28 split cpu and created more power schema
2019-11-05 added bom
2019-11-07 finishing schematic
2019-11-08 finished fixes
2019-11-11 Power done
2019-11-12 Finished all except RAM and CPU
2019-11-13 fixed fanout
2019-11-18 first gbrs

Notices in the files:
parts and their libraries:
Copyright 2016 Accelerated Designs. All rights reserved.
